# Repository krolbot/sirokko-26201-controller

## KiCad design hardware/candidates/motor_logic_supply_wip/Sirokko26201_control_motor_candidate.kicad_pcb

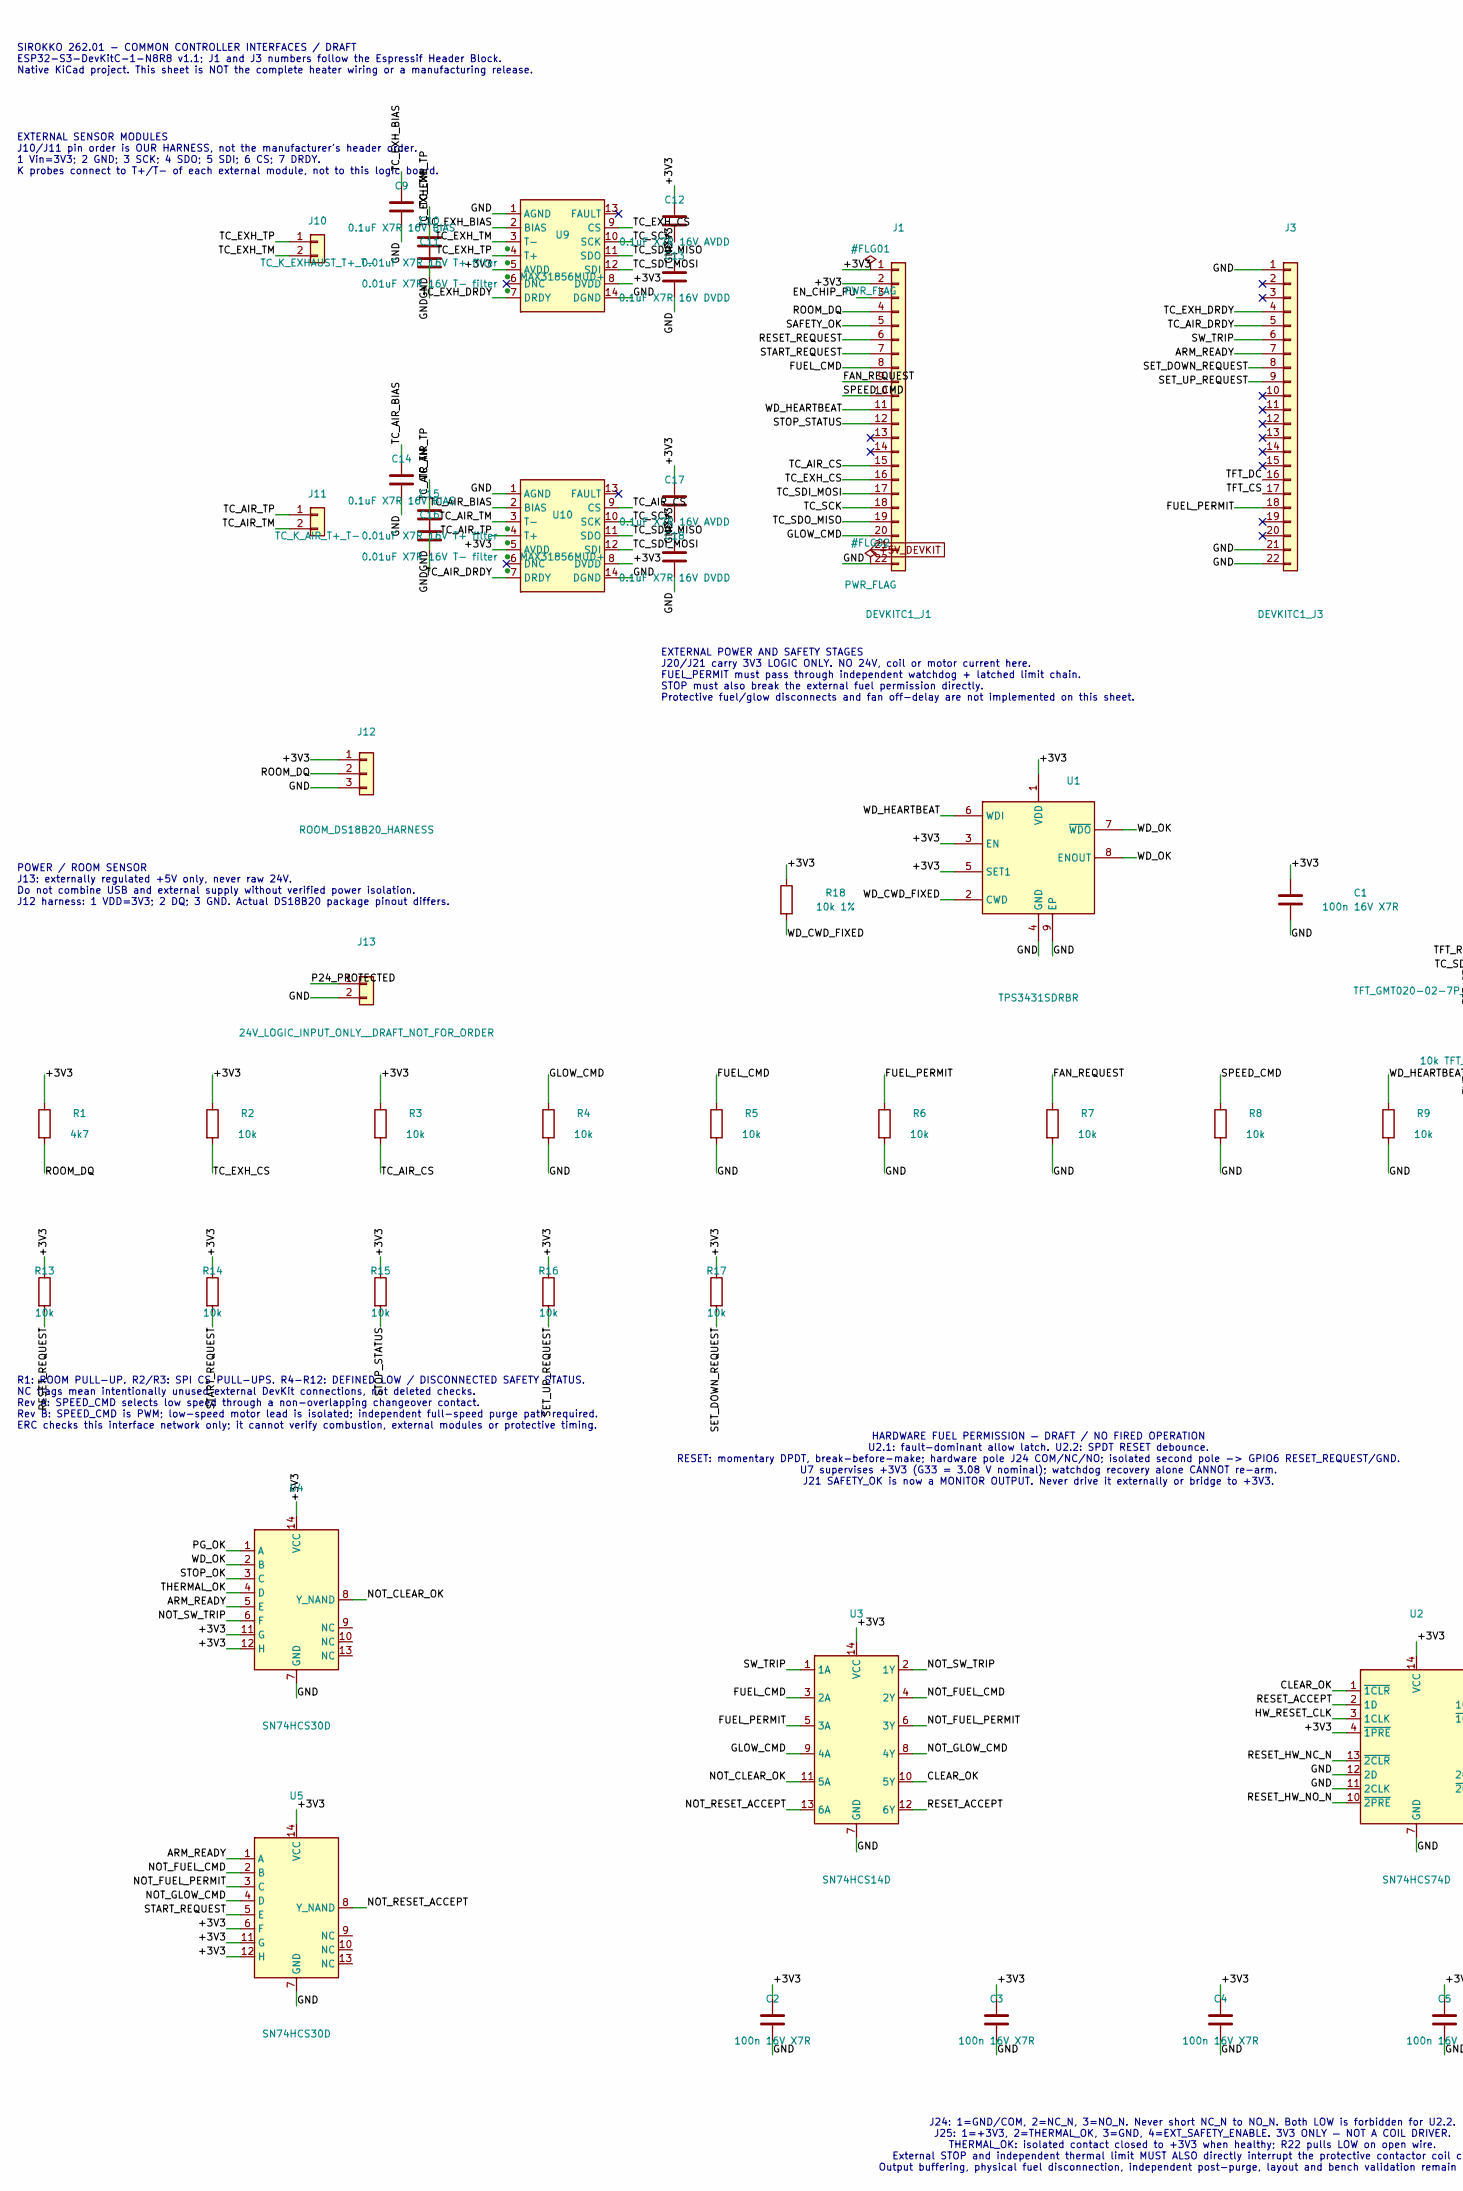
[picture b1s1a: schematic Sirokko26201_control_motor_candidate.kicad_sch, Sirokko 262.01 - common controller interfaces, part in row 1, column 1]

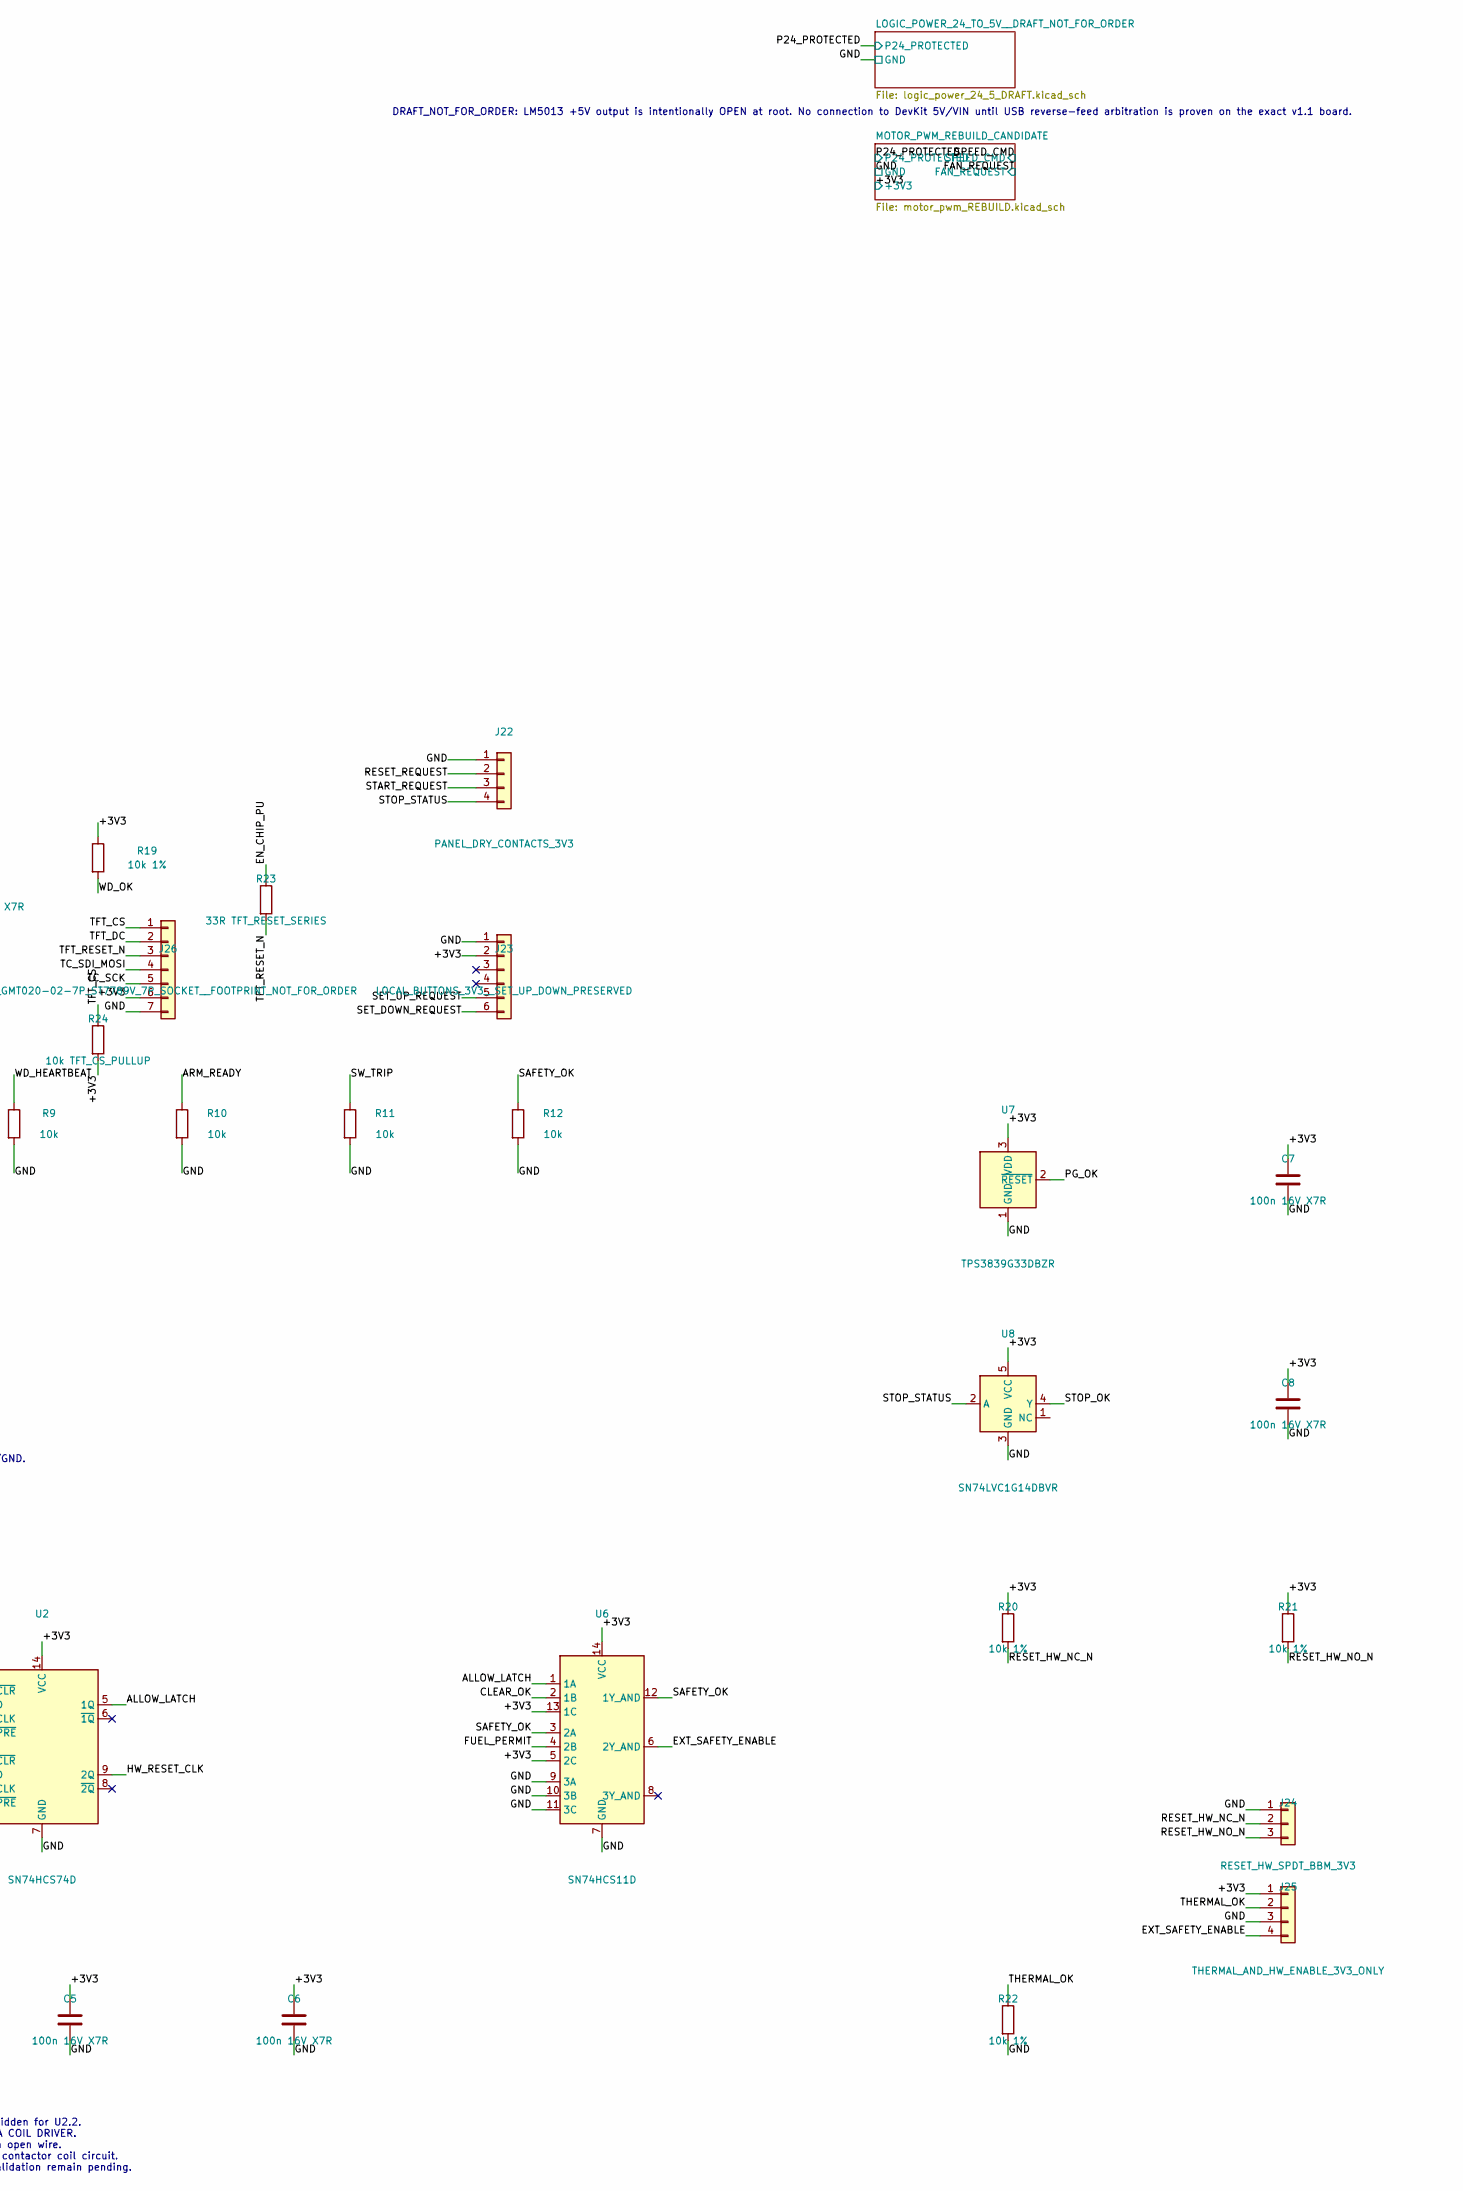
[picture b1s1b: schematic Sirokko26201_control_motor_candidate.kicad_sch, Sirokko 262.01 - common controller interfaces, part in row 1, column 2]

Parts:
C1, C2, C3, C4, C5, C6, C7, C8: 100n 16V X7R; C_0603_1608Metric
C9, C14: 0.1uF X7R 16V BIAS; C_0603_1608Metric
C10, C15: 0.01uF X7R 16V T+ filter; C_0603_1608Metric
C11, C16: 0.01uF X7R 16V T- filter; C_0603_1608Metric
C12, C17: 0.1uF X7R 16V AVDD; C_0603_1608Metric
C13, C18: 0.1uF X7R 16V DVDD; C_0603_1608Metric
J1: DEVKITC1_J1; PinSocket_1x22_P2.54mm_Vertical
J3: DEVKITC1_J3; PinSocket_1x22_P2.54mm_Vertical
J10: TC_K_EXHAUST_T+_T-; TerminalBlock_Phoenix_MKDS-1,5-2-5.08_1x02_P5.08mm_Horizont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
J11: TC_K_AIR_T+_T-; TerminalBlock_Phoenix_MKDS-1,5-2-5.08_1x02_P5.08mm_Horizont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
J12: ROOM_DS18B20_HARNESS; TerminalBlock_Phoenix_MKDS-1,5-3-5.08_1x03_P5.08mm_Horizont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
J13: 24V_LOGIC_INPUT_ONLY__DRAFT_NOT_FOR_ORDER; TerminalBlock_Phoenix_MKDS-1,5-2-5.08_1x02_P5.08mm_Horizont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
J22: PANEL_DRY_CONTACTS_3V3; TerminalBlock_Phoenix_MKDS-1,5-4-5.08_1x04_P5.08mm_Horizont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
J23: LOCAL_BUTTONS_3V3__SET_UP_DOWN_PRESERVED; TerminalBlock_Phoenix_MKDS-1,5-6_1x06_P5.00mm_Horizontal
J24: RESET_HW_SPDT_BBM_3V3; TerminalBlock_Phoenix_MKDS-1,5-3-5.08_1x03_P5.08mm_Horizont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
J25: THERMAL_AND_HW_ENABLE_3V3_ONLY; TerminalBlock_Phoenix_MKDS-1,5-4-5.08_1x04_P5.08mm_Horizont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
J26: TFT_GMT020-02-7P_ST7789V_7P_SOCKET__FOOTPRINT_NOT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; PinSocket_1x07_P2.54mm_Vertical
R1: 4k7; R_Axial_DIN0207_L6.3mm_D2.5mm_P10.16mm_Horizontal
R2, R3, R4, R5, R6, R7, R8, R9, R10, R11, R12, R13, R14, R15, R16, R17: 10k; R_Axial_DIN0207_L6.3mm_D2.5mm_P10.16mm_Horizontal
R18, R19, R20, R21, R22: 10k 1%; R_0603_1608Metric
R23: 33R TFT_RESET_SERIES; R_0603_1608Metric
R24: 10k TFT_CS_PULLUP; R_0603_1608Metric
U1: TPS3431SDRBR; TPS3431_DRB0008A
U2: SN74HCS74D; SOIC-14_3.9x8.7mm_P1.27mm
U3: SN74HCS14D; SOIC-14_3.9x8.7mm_P1.27mm
U4, U5: SN74HCS30D; SOIC-14_3.9x8.7mm_P1.27mm
U6: SN74HCS11D; SOIC-14_3.9x8.7mm_P1.27mm
U7: TPS3839G33DBZR; SOT-23
U8: SN74LVC1G14DBVR; SOT-23-5
U9, U10: MAX31856MUD+; MPN MAX31856MUD+

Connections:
+5V_DEVKIT: J1.21; also elsewhere on the board
/+3V3: C1.1, C2.1, C3.1, C4.1, C5.1, C6.1, C7.1, C8.1, C12.1, C13.1, C17.1, C18.1, J1.1, J1.2, J12.1, J23.2, J25.1, J26.6, R1.1, R2.1, R3.1, R13.1, R14.1, R15.1, R16.1, R17.1, R18.1, R19.1, R20.1, R21.1, R24.2, U1.1 (VDD), U1.3 (EN), U1.5 (SET1), U2.4 (~1PRE), U2.14 (VCC), U3.14 (VCC), U4.11 (G), U4.12 (H), U4.14 (VCC), U5.6 (F), U5.11 (G), U5.12 (H), U5.14 (VCC), U6.5 (2C), U6.13 (1C), U6.14 (VCC), U7.3 (VDD), U8.5 (VCC), U9.5 (AVDD), U9.8 (DVDD), U10.5 (AVDD), U10.8 (DVDD); also elsewhere on the board
/ALLOW_LATCH: U2.5 (1Q), U6.1 (1A)
/ARM_READY: J3.7, R10.1, U4.5 (E), U5.1 (A)
/CLEAR_OK: U2.1 (~1CLR), U3.10 (5Y), U6.2 (1B)
/EN_CHIP_PU: J1.3, R23.1
/EXT_SAFETY_ENABLE: J25.4, U6.6 (2Y_AND)
/FAN_REQUEST: J1.9, R7.1; also elsewhere on the board
/FUEL_CMD: J1.8, R5.1, U3.3 (2A)
/FUEL_PERMIT: J3.18, R6.1, U3.5 (3A), U6.4 (2B)
/GLOW_CMD: J1.20, R4.1, U3.9 (4A)
/GND: C1.2, C2.2, C3.2, C4.2, C5.2, C6.2, C7.2, C8.2, C9.2, C10.2, C11.2, C12.2, C13.2, C14.2, C15.2, C16.2, C17.2, C18.2, J1.22, J3.1, J3.21, J3.22, J12.3, J13.2, J22.1, J23.1, J24.1, J25.3, J26.7, R4.2, R5.2, R6.2, R7.2, R8.2, R9.2, R10.2, R11.2, R12.2, R22.2, U1.4 (GND), U1.9 (EP), U2.7 (GND), U2.11 (2CLK), U2.12 (2D), U3.7 (GND), U4.7 (GND), U5.7 (GND), U6.7 (GND), U6.9 (3A), U6.10 (3B), U6.11 (3C), U7.1 (GND), U8.3 (GND), U9.1 (AGND), U9.14 (DGND), U10.1 (AGND), U10.14 (DGND); also elsewhere on the board
/HW_RESET_CLK: U2.3 (1CLK), U2.9 (2Q)
/NOT_CLEAR_OK: U3.11 (5A), U4.8 (Y_NAND)
/NOT_FUEL_CMD: U3.4 (2Y), U5.2 (B)
/NOT_FUEL_PERMIT: U3.6 (3Y), U5.3 (C)
/NOT_GLOW_CMD: U3.8 (4Y), U5.4 (D)
/NOT_RESET_ACCEPT: U3.13 (6A), U5.8 (Y_NAND)
/NOT_SW_TRIP: U3.2 (1Y), U4.6 (F)
/P24_PROTECTED: J13.1; also elsewhere on the board
/PG_OK: U4.1 (A), U7.2 (~RESET)
/RESET_ACCEPT: U2.2 (1D), U3.12 (6Y)
/RESET_HW_NC_N: J24.2, R20.2, U2.13 (~2CLR)
/RESET_HW_NO_N: J24.3, R21.2, U2.10 (~2PRE)
/RESET_REQUEST: J1.6, J22.2, R13.2
/ROOM_DQ: J1.4, J12.2, R1.2
/SAFETY_OK: J1.5, R12.1, U6.3 (2A), U6.12 (1Y_AND)
/SET_DOWN_REQUEST: J3.8, J23.6, R17.2
/SET_UP_REQUEST: J3.9, J23.5, R16.2
/SPEED_CMD: J1.10, R8.1; also elsewhere on the board
/START_REQUEST: J1.7, J22.3, R14.2, U5.5 (E)
/STOP_OK: U4.3 (C), U8.4 (Y)
/STOP_STATUS: J1.12, J22.4, R15.2, U8.2 (A)
/SW_TRIP: J3.6, R11.1, U3.1 (1A)
/TC_AIR_BIAS: C14.1, U10.2 (BIAS)
/TC_AIR_CS: J1.15, R3.2, U10.9 (CS)
/TC_AIR_DRDY: J3.5, U10.7 (DRDY)
/TC_AIR_TM: C16.1, J11.2, U10.3 (T-)
/TC_AIR_TP: C15.1, J11.1, U10.4 (T+)
/TC_EXH_BIAS: C9.1, U9.2 (BIAS)
/TC_EXH_CS: J1.16, R2.2, U9.9 (CS)
/TC_EXH_DRDY: J3.4, U9.7 (DRDY)
/TC_EXH_TM: C11.1, J10.2, U9.3 (T-)
/TC_EXH_TP: C10.1, J10.1, U9.4 (T+)
/TC_SCK: J1.18, J26.5, U9.10 (SCK), U10.10 (SCK)
/TC_SDI_MOSI: J1.17, J26.4, U9.12 (SDI), U10.12 (SDI)
/TC_SDO_MISO: J1.19, U9.11 (SDO), U10.11 (SDO)
/TFT_CS: J3.17, J26.1, R24.1
/TFT_DC: J3.16, J26.2
/TFT_RESET_N: J26.3, R23.2
/THERMAL_OK: J25.2, R22.1, U4.4 (D)
/WD_CWD_FIXED: R18.2, U1.2 (CWD)
/WD_HEARTBEAT: J1.11, R9.1, U1.6 (WDI)
/WD_OK: R19.2, U1.7 (~WDO), U1.8 (ENOUT), U4.2 (B)

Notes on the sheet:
SIROKKO 262.01 - COMMON CONTROLLER INTERFACES / DRAFT ESP32-S3-DevKitC-1-N8R8 v1.1; J1 and J3 numbers follow the Espressif Header Block. Native KiCad project. This sheet is NOT the complete heater wiring or a manufacturing release.
EXTERNAL SENSOR MODULES J10/J11 pin order is OUR HARNESS, not the manufacturer's header order. 1 Vin=3V3; 2 GND; 3 SCK; 4 SDO; 5 SDI; 6 CS; 7 DRDY. K probes connect to T+/T- of each external module, not to this logic board.
EXTERNAL POWER AND SAFETY STAGES J20/J21 carry 3V3 LOGIC ONLY. NO 24V, coil or motor current here. FUEL_PERMIT must pass through independent watchdog + latched limit chain. STOP must also break the external fuel permission directly. Protective fuel/glow disconnects and fan off-delay are not impleme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
POWER / ROOM SENSOR J13: externally regulated +5V only, never raw 24V. Do not combine USB and external supply without verified power isolation. J12 harness: 1 VDD=3V3; 2 DQ; 3 GND. Actual DS18B20 package pinout differs.
R1: ROOM PULL-UP. R2/R3: SPI CS PULL-UPS. R4-R12: DEFINED LOW / DISCONNECTED SAFETY STATUS. NC flags mean intentionally unused external DevKit connections, not deleted checks. Rev A: SPEED_CMD selects low speed through a non-overlapping changeover contact. Rev B: SPEED_CMD is PWM; low-speed motor l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
HARDWARE FUEL PERMISSION — DRAFT / NO FIRED OPERATION U2.1: fault-dominant allow latch. U2.2: SPDT RESET debounce. RESET: momentary DPDT, break-before-make; hardware pole J24 COM/NC/NO; isolated second pole -> GPIO6 RESET_REQUEST/GND. U7 supervises +3V3 (G33 = 3.08 V nominal); watchdog recovery alo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
J24: 1=GND/COM, 2=NC_N, 3=NO_N. Never short NC_N to NO_N. Both LOW is forbidden for U2.2. J25: 1=+3V3, 2=THERMAL_OK, 3=GND, 4=EXT_SAFETY_ENABLE. 3V3 ONLY — NOT A COIL DRIVER. THERMAL_OK: isolated contact closed to +3V3 when healthy; R22 pulls LOW on open wire. External STOP and independent thermal 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
DRAFT_NOT_FOR_ORDER: LM5013 +5V output is intentionally OPEN at root. No connection to DevKit 5V/VIN until USB reverse-feed arbitration is proven on the exact v1.1 board.

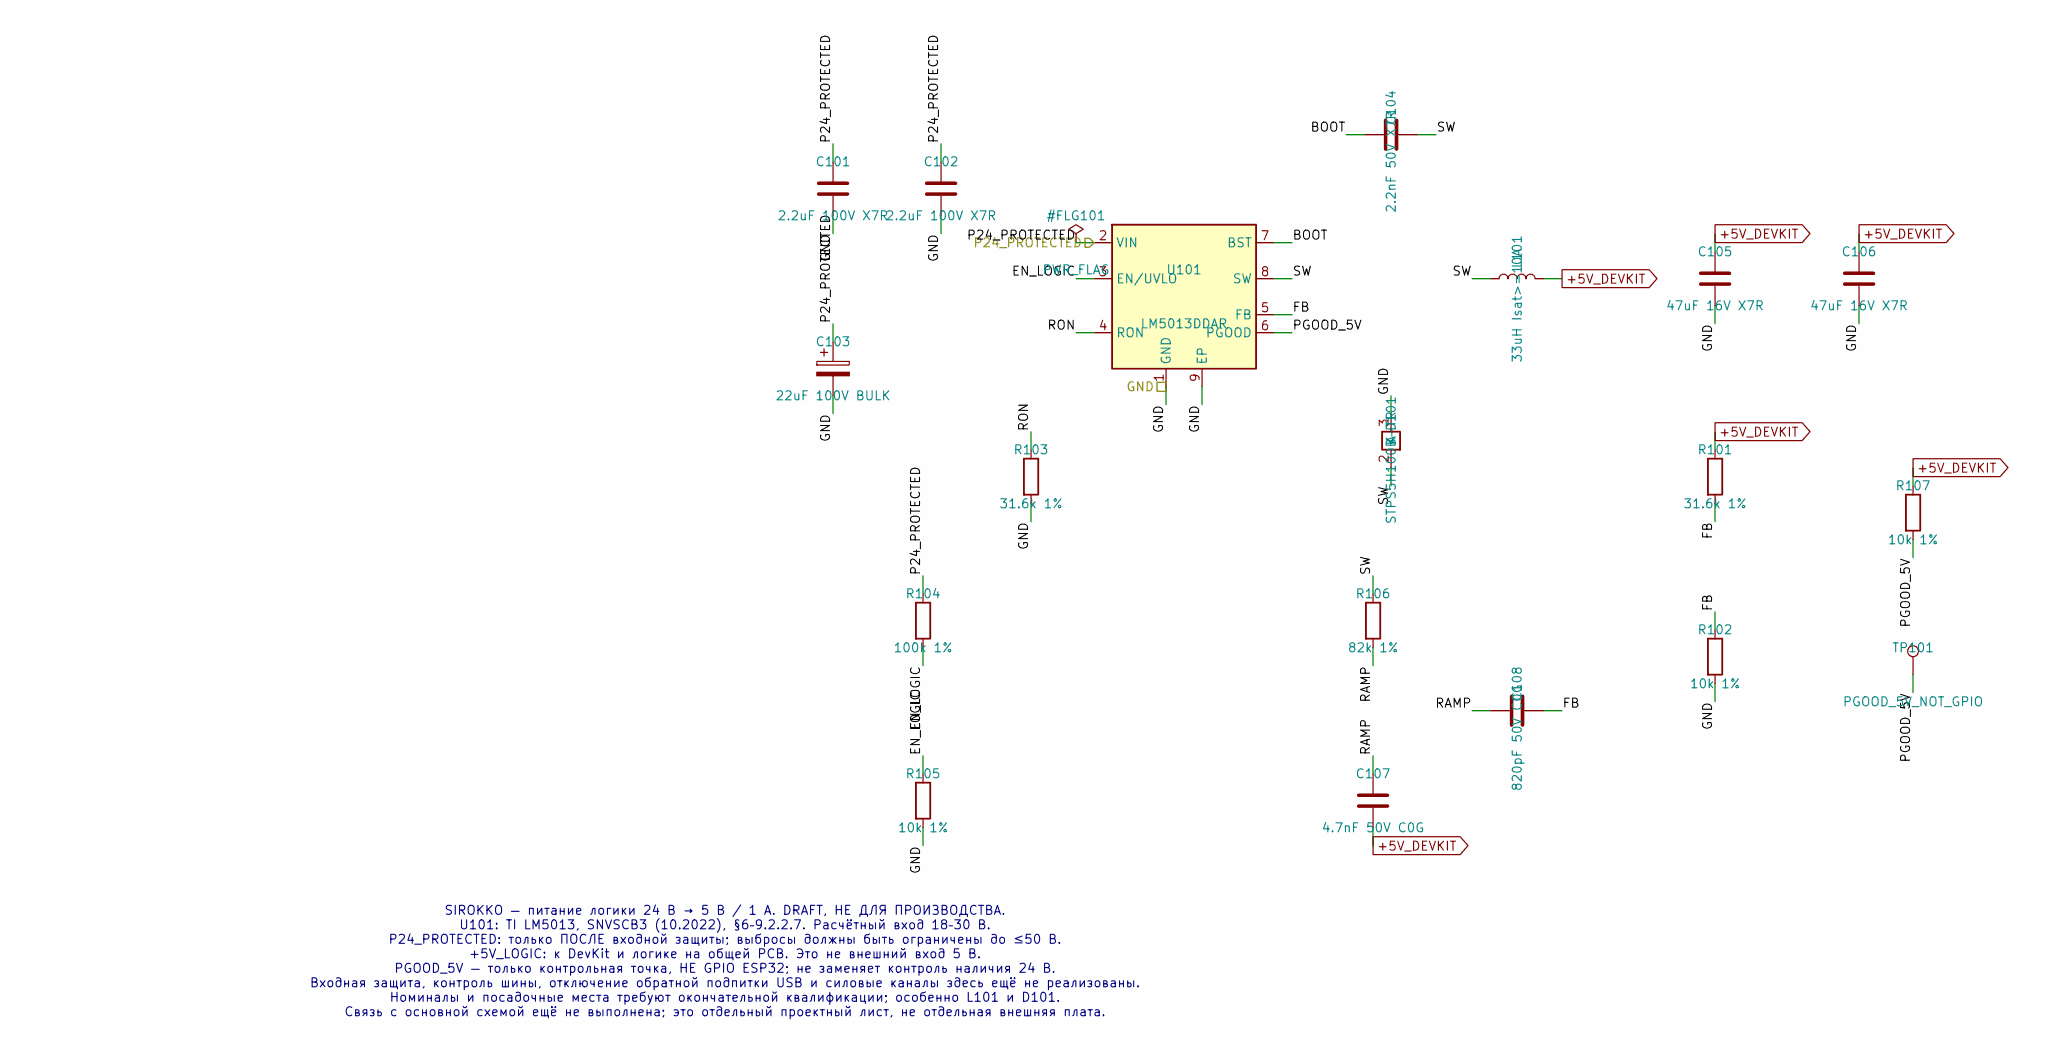
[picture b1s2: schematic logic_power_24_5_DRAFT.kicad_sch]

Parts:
C101, C102: 2.2uF 100V X7R; C_1210_3225Metric; MPN GRM32ER72A225KA35L
C103: 22uF 100V BULK; C_1210_3225Metric; MPN GRM32ER72A226KE20L
C104: 2.2nF 50V X7R; C_0603_1608Metric; MPN CC0603KRX7R9BB222
C105, C106: 47uF 16V X7R; C_1210_3225Metric; MPN GRM32ER61C476KE15L
C107: 4.7nF 50V C0G; C_0603_1608Metric; MPN GRM1885C1H472JA01D
C108: 820pF 50V C0G; C_0603_1608Metric; MPN CC0603JRNPO9BN821
D101: STPS5H100B-TR; MPN STPS5H100B-TR
L101: 33uH Isat>=10A; L_Bourns_SRP1770TA_16.9x16.9mm; MPN SRP1770TA-330M
R101, R103: 31.6k 1%; R_0603_1608Metric; MPN RC0603FR-0731K6L
R102, R105, R107: 10k 1%; R_0603_1608Metric; MPN RC0603FR-0710KL
R104: 100k 1%; R_0603_1608Metric; MPN RC0603FR-07100KL
R106: 82k 1%; R_0603_1608Metric; MPN RC0603FR-0782KL
TP101: PGOOD_5V_NOT_GPIO; TestPoint_Keystone_5015_Micro_Mini; MPN 5015
U101: LM5013DDAR; DDA0008B_LM5013DDAR_TI4214849B

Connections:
+5V_DEVKIT: C105.1, C106.1, C107.2, L101.2, R101.1, R107.1; also elsewhere on the board
/GND: C101.2, C102.2, C103.2, C105.2, C106.2, D101.3 (A), R102.2, R103.2, R105.2, U101.1 (GND), U101.9 (EP); also elsewhere on the board
/LOGIC_POWER_24_TO_5V__DRAFT_NOT_FOR_ORDER/BOOT: C104.1, U101.7 (BST)
/LOGIC_POWER_24_TO_5V__DRAFT_NOT_FOR_ORDER/EN_LOGIC: R104.2, R105.1, U101.3 (EN/UVLO)
/LOGIC_POWER_24_TO_5V__DRAFT_NOT_FOR_ORDER/FB: C108.2, R101.2, R102.1, U101.5 (FB)
/LOGIC_POWER_24_TO_5V__DRAFT_NOT_FOR_ORDER/PGOOD_5V: R107.2, TP101.1, U101.6 (PGOOD)
/LOGIC_POWER_24_TO_5V__DRAFT_NOT_FOR_ORDER/RAMP: C107.1, C108.1, R106.2
/LOGIC_POWER_24_TO_5V__DRAFT_NOT_FOR_ORDER/RON: R103.1, U101.4 (RON)
/LOGIC_POWER_24_TO_5V__DRAFT_NOT_FOR_ORDER/SW: C104.2, D101.2 (K), L101.1, R106.1, U101.8 (SW)
/P24_PROTECTED: C101.1, C102.1, C103.1, R104.1, U101.2 (VIN); also elsewhere on the board

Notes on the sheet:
SIROKKO — питание логики 24 В → 5 В / 1 А. DRAFT, НЕ ДЛЯ ПРОИЗВОДСТВА. U101: TI LM5013, SNVSCB3 (10.2022), §6–9.2.2.7. Расчётный вход 18–30 В. P24_PROTECTED: только ПОСЛЕ входной защиты; выбросы должны быть ограничены до ≤50 В. +5V_LOGIC: к DevKit и логике на общей PCB. Это не внешний вход 5 В. PGO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

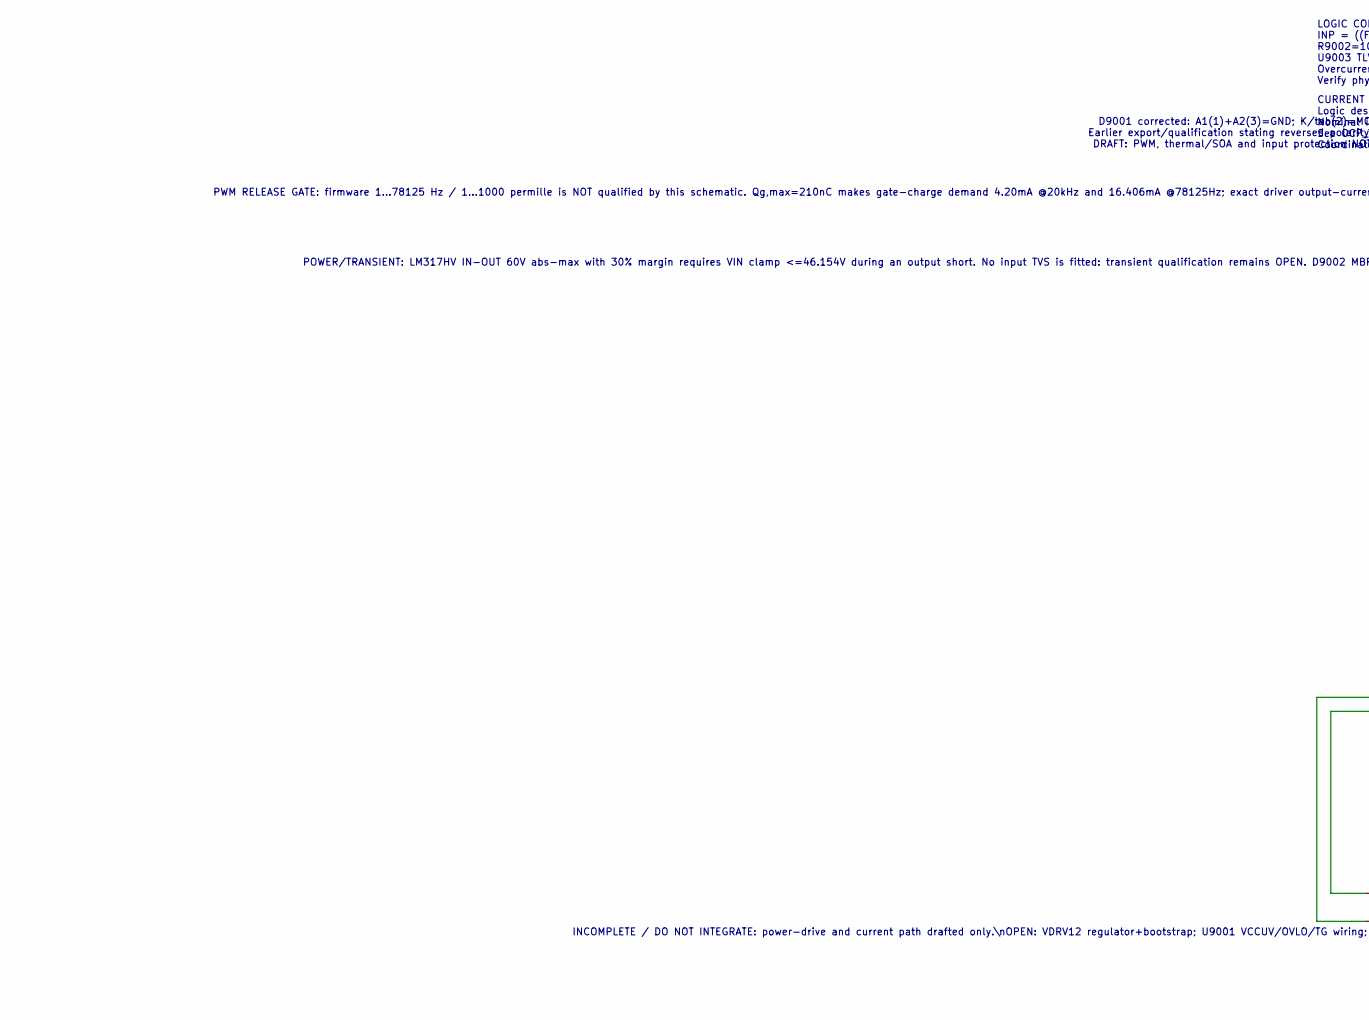
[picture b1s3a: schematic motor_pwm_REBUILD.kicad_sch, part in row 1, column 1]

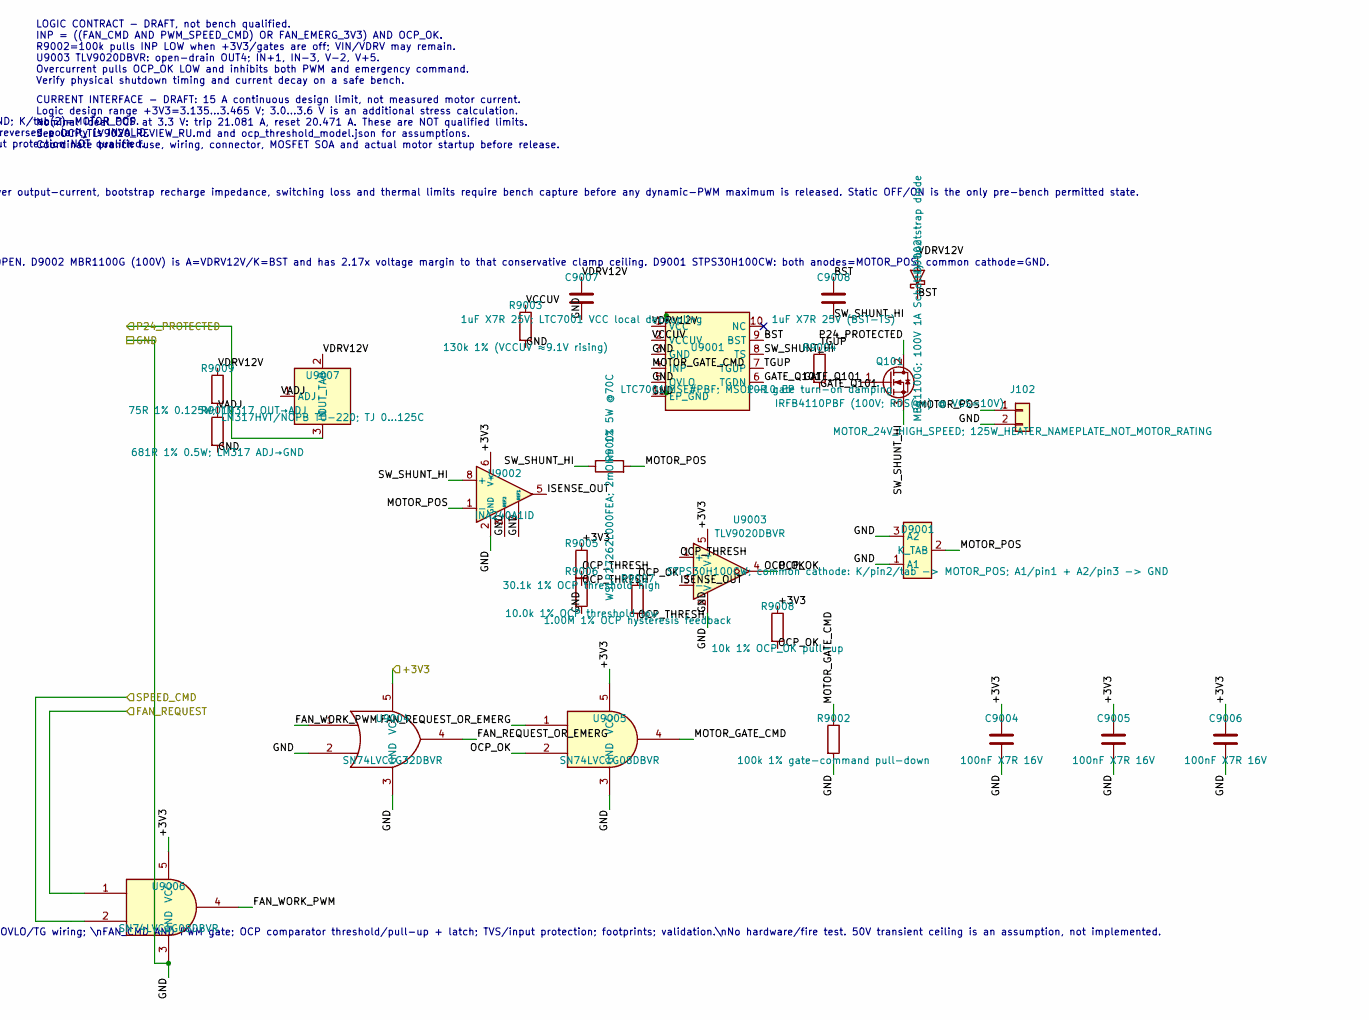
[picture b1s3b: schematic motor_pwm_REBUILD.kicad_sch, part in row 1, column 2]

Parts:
C9004, C9005, C9006: 100nF X7R 16V; C_0603_1608Metric
C9007: 1uF X7R 25V; LTC7001 VCC local decoupling; C_0805_2012Metric
C9008: 1uF X7R 25V (BST-TS); C_0805_2012Metric
D9001: STPS30H100CW; common cathode: K/pin2/tab -> MOTOR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; TO-220-3_Vertical; MPN STPS30H100CW
D9002: MBR1100G; 100V 1A Schottky bootstrap diode; D_DO-41_SOD81_P10.16mm_Horizontal; MPN MBR1100G
J102: MOTOR_24V_HIGH_SPEED; 125W_HEATER_NAMEPLATE_NOT_M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; TerminalBlock_Phoenix_MKDS-1,5-2-5.08_1x02_P5.08mm_Horizont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
Q101: IRFB4110PBF (100V; RDS(on) @ VGS=10V); TO-220-3_Vertical
R9001: WSLP27262L000FEA; 2mOhm 1% 5W @70C; WSLP2726
R9002: 100k 1% gate-command pull-down; R_0603_1608Metric
R9003: 130k 1% (VCCUV ≈9.1V rising); R_0603_1608Metric
R9004: 10R gate turn-on damping; R_0603_1608Metric
R9005: 30.1k 1% OCP threshold high; R_0603_1608Metric
R9006: 10.0k 1% OCP threshold low; R_0603_1608Metric
R9007: 1.00M 1% OCP hysteresis feedback; R_0603_1608Metric
R9008: 10k 1% OCP_OK pull-up; R_0603_1608Metric
R9009: 75R 1% 0.125W; LM317 OUT→ADJ; R_0805_2012Metric
R9010: 681R 1% 0.5W; LM317 ADJ→GND; R_2010_5025Metric
U9001: LTC7001IMSE#PBF; MSOP-10 EP; MSOP-10-1EP_3x3mm_P0.5mm_EP1.68x1.88mm
U9002: INA240A1ID; SOIC-8_3.9x4.9mm_P1.27mm
U9003: TLV9020DBVR; SOT-23-5
U9004: SN74LVC1G32DBVR; SOT-23-5
U9005, U9006: SN74LVC1G08DBVR; SOT-23-5
U9007: LM317HVT/NOPB TO-220; TJ 0…125C; TO-220-3_Vertical

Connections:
/+3V3: C9004.1, C9005.1, C9006.1, R9005.1, R9008.1, U9002.6 (V+), U9003.5 (V+), U9004.5 (VCC), U9005.5 (VCC), U9006.5 (VCC); also elsewhere on the board
/FAN_REQUEST: U9006.1; also elsewhere on the board
/GND: C9004.2, C9005.2, C9006.2, C9007.2, D9001.1 (A1), D9001.3 (A2), J102.2, R9002.2, R9003.2, R9006.2, R9010.2, U9001.3 (GND), U9001.5 (OVLO), U9001.11 (EP_GND), U9002.2 (GND), U9002.3 (REF2), U9002.4 (GND), U9002.7 (REF1), U9003.2 (V-), U9004.2, U9004.3 (GND), U9005.3 (GND), U9006.3 (GND); also elsewhere on the board
/MOTOR_PWM_REBUILD_CANDIDATE/BST: C9008.1, D9002.1 (K), U9001.9 (BST)
/MOTOR_PWM_REBUILD_CANDIDATE/FAN_REQUEST_OR_EMERG: U9004.4, U9005.1
/MOTOR_PWM_REBUILD_CANDIDATE/FAN_WORK_PWM: U9004.1, U9006.4
/MOTOR_PWM_REBUILD_CANDIDATE/GATE_Q101: Q101.1 (G), R9004.2, U9001.6 (TGDN)
/MOTOR_PWM_REBUILD_CANDIDATE/ISENSE_OUT: U9002.5, U9003.3 (-)
/MOTOR_PWM_REBUILD_CANDIDATE/MOTOR_GATE_CMD: R9002.1, U9001.4 (INP), U9005.4
/MOTOR_PWM_REBUILD_CANDIDATE/MOTOR_POS: D9001.2 (K_TAB), J102.1, R9001.2, U9002.1 (-)
/MOTOR_PWM_REBUILD_CANDIDATE/OCP_OK: R9007.1, R9008.2, U9003.4, U9005.2
/MOTOR_PWM_REBUILD_CANDIDATE/OCP_THRESH: R9005.2, R9006.1, R9007.2, U9003.1 (+)
/MOTOR_PWM_REBUILD_CANDIDATE/SW_SHUNT_HI: C9008.2, Q101.3 (S), R9001.1, U9001.8 (TS), U9002.8 (+)
/MOTOR_PWM_REBUILD_CANDIDATE/TGUP: R9004.1, U9001.7 (TGUP)
/MOTOR_PWM_REBUILD_CANDIDATE/VADJ: R9009.2, R9010.1, U9007.1 (ADJ)
/MOTOR_PWM_REBUILD_CANDIDATE/VCCUV: R9003.1, U9001.2 (VCCUV)
/MOTOR_PWM_REBUILD_CANDIDATE/VDRV12V: C9007.1, D9002.2 (A), R9009.1, U9001.1 (VCC), U9007.2 (OUT_TAB)
/P24_PROTECTED: Q101.2 (D), U9007.3 (IN); also elsewhere on the board
/SPEED_CMD: U9006.2; also elsewhere on the board

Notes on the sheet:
INCOMPLETE / DO NOT INTEGRATE: power-drive and current path drafted only.\nOPEN: VDRV12 regulator+bootstrap; U9001 VCCUV/OVLO/TG wiring; \nFAN_CMD AND PWM gate; OCP comparator threshold/pull-up + latch; TVS/input protection; footprints; validation.\nNo hardware/fire test. 50V transient ceiling is a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
LOGIC CONTRACT - DRAFT, not bench qualified. INP = ((FAN_CMD AND PWM_SPEED_CMD) OR FAN_EMERG_3V3) AND OCP_OK. R9002=100k pulls INP LOW when +3V3/gates are off; VIN/VDRV may remain. U9003 TLV9020DBVR: open-drain OUT4; IN+1, IN-3, V-2, V+5. Overcurrent pulls OCP_OK LOW and inhibits both PWM and emerg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
CURRENT INTERFACE - DRAFT: 15 A continuous design limit, not measured motor current. Logic design range +3V3=3.135...3.465 V; 3.0...3.6 V is an additional stress calculation. Nominal ideal OCP at 3.3 V: trip 21.081 A, reset 20.471 A. These are NOT qualified limits. See OCP_TLV9020_REVIEW_RU.md and 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
PWM RELEASE GATE: firmware 1…78125 Hz / 1…1000 permille is NOT qualified by this schematic. Qg,max=210nC makes gate-charge demand 4.20mA @20kHz and 16.406mA @78125Hz; exact driver output-current, bootstrap recharge impedance, switching loss and thermal limits require bench capture before any dynami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
POWER/TRANSIENT: LM317HV IN-OUT 60V abs-max with 30% margin requires VIN clamp <=46.154V during an output short. No input TVS is fitted: transient qualification remains OPEN. D9002 MBR1100G (100V) is A=VDRV12V/K=BST and has 2.17x voltage margin to that conservative clamp ceiling. D9001 STPS30H100CW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
D9001 corrected: A1(1)+A2(3)=GND; K/tab(2)=MOTOR_POS. Earlier export/qualification stating reversed polarity is INVALID. DRAFT: PWM, thermal/SOA and input protection NOT qualified.

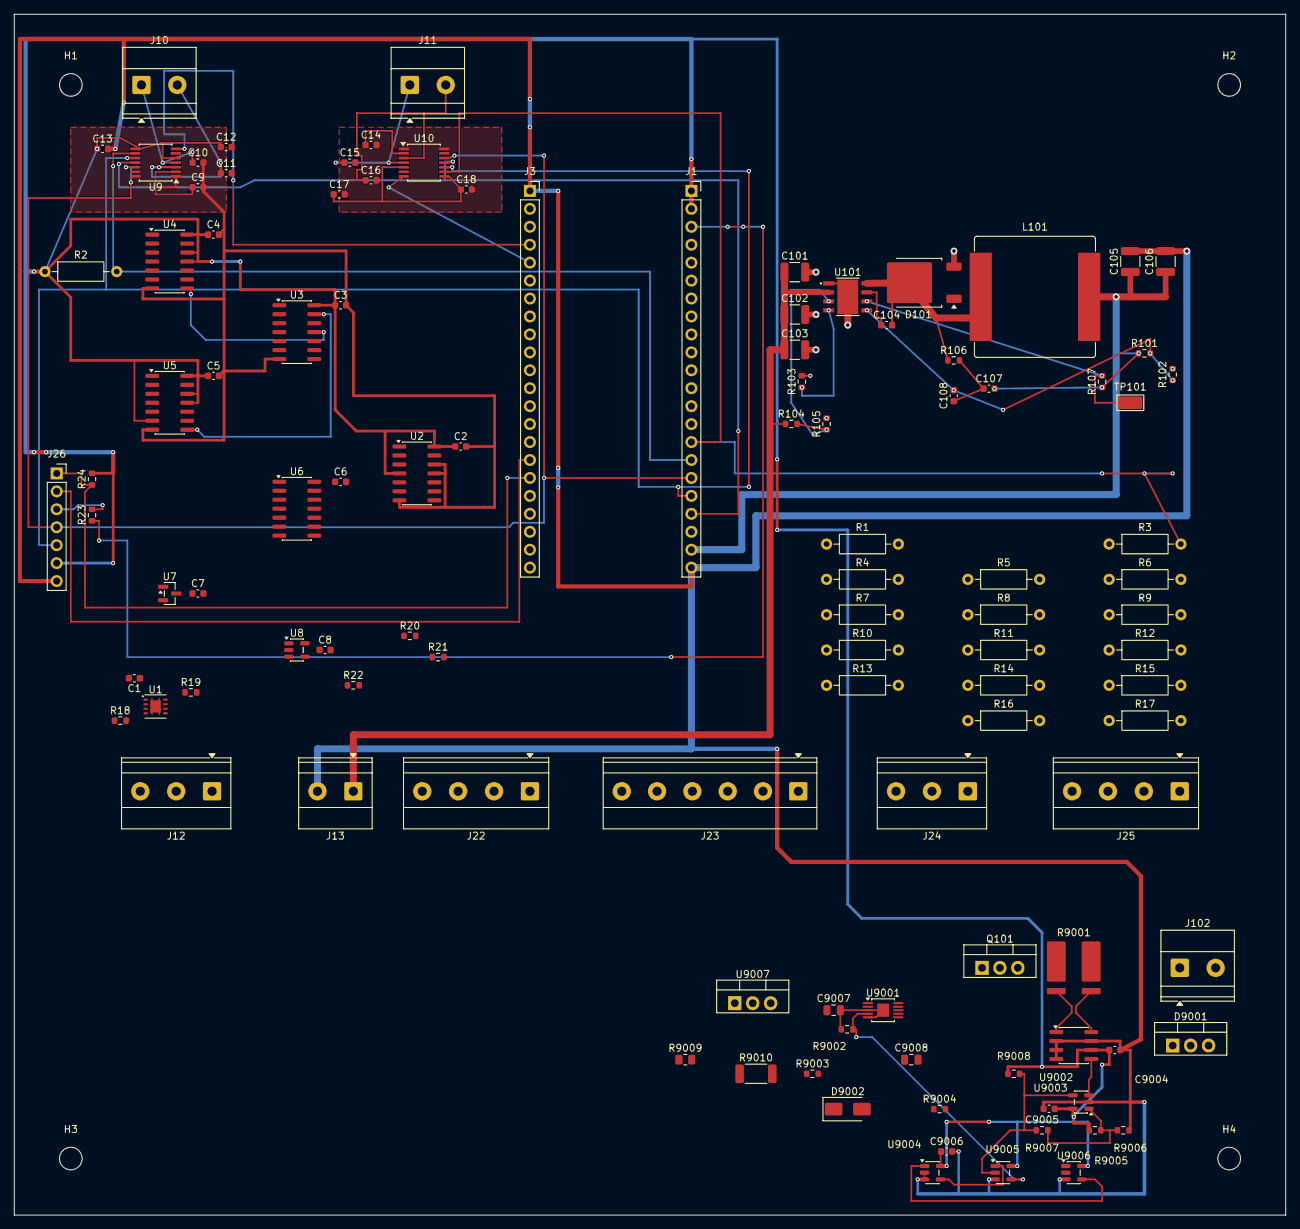
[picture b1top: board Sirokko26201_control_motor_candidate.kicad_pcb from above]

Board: 2 copper layers, 180.0 x 170.0 mm, 112 parts (0 on the bottom side), 75 nets.

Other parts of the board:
H1, H2, H3, H4: M3; MountingHole_3.2mm_M3
